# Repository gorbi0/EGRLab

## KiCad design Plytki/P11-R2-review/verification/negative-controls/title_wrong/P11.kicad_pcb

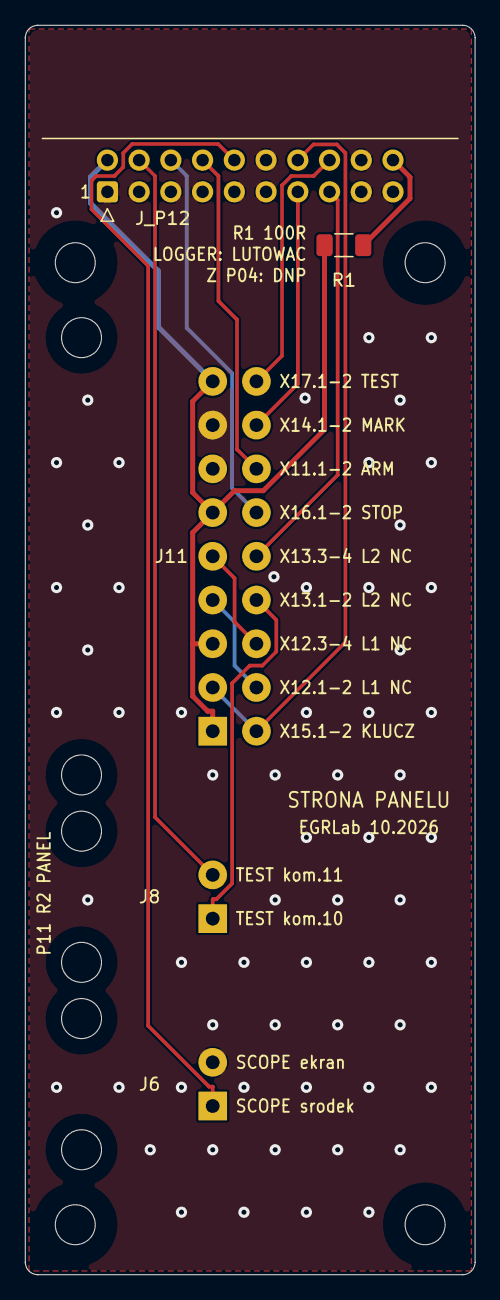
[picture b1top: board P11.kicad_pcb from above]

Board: 2 copper layers, 36.0 x 100.0 mm, 9 parts (0 on the bottom side), 14 nets.

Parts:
H1, H2, H3, H4: M3 NPTH
J6: SCOPE tail; FIELD_PAIR2
J8: TEST signal; FIELD_PAIR2
J11: CONTACTS; FIELD_CONTACT18
J_P12: IDC 2x10 katowe do P12; IDC-Header_2x10_P2.54mm_Horizontal
R1: 100R; R_1206_3216Metric_Pad1.30x1.75mm_HandSolder

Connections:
/3V3_IO: J_P12.20, R1.1
/CONTACTS/DIAG_L1_L2: J11.6, J11.9
/CONTACTS/ILK_L1_L2: J11.4, J11.7
/CONTACTS/LOOP_OUT: J8.1, J11.8
/N_J_SCOPE_HOT: J6.1, J_P12.10
ARM_CONTACT: J11.14, J_P12.8
GND: J6.2, J11.13, J11.15, J_P12.1, J_P12.3, J_P12.5, J_P12.7, J_P12.9, J_P12.11, J_P12.12, J_P12.17, J_P12.18, J_P12.19
LOGGER_CLEAR: J11.10, J_P12.15
MARK: J11.16, J_P12.13
MECH_OK: J8.2, J_P12.4
PANEL_3V3: J11.1, J11.5, J11.11, J11.17, J_P12.2, R1.2
STOP_NC_OUT: J11.12, J_P12.6
TEST_KEY: J11.2, J11.3, J_P12.14
TEST_PRESENT: J11.18, J_P12.16

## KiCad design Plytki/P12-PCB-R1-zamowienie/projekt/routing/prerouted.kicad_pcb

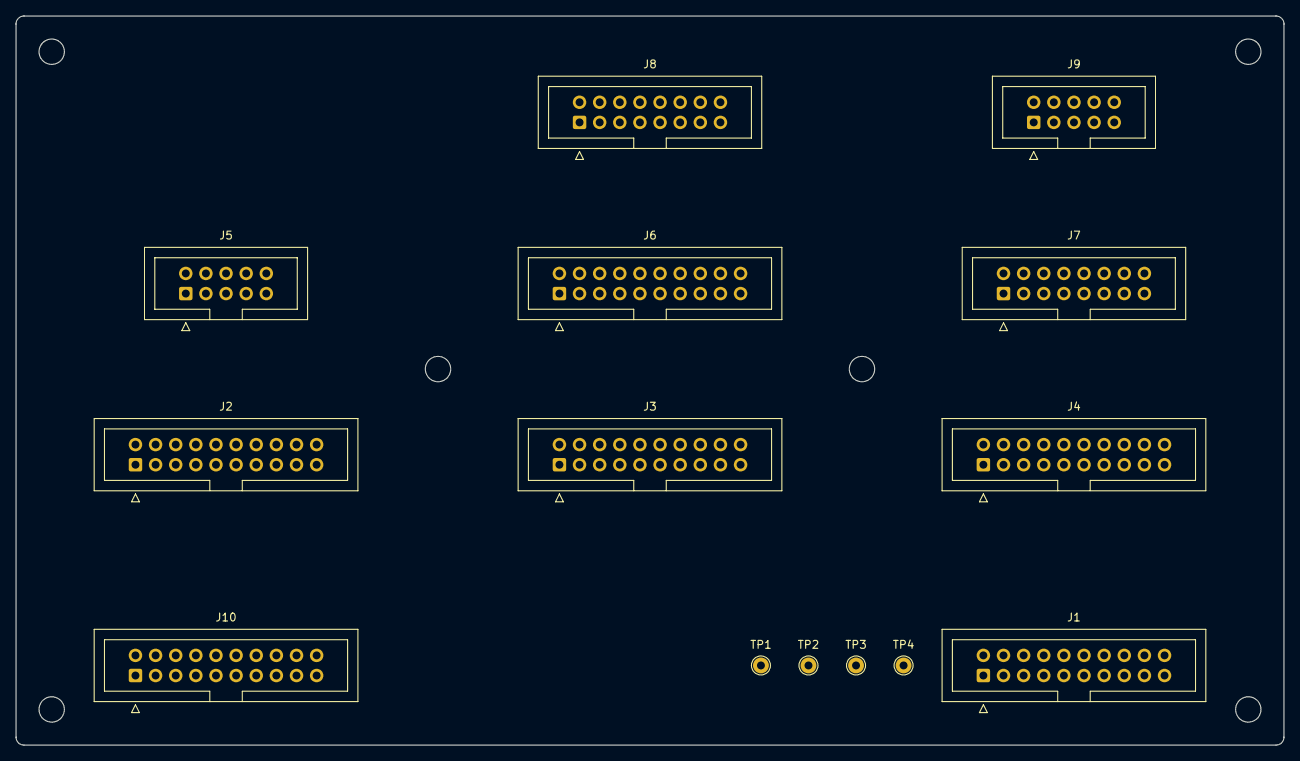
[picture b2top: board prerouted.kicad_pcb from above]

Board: 2 copper layers, 160.0 x 92.0 mm, 20 parts (0 on the bottom side), 27 nets, no tracks yet.

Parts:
H1, H2, H3, H4, H5, H6: M3 NPTH
J1: P02 J_BP; IDC-Header_2x10_P2.54mm_Vertical
J2: P03 J_BP1; IDC-Header_2x10_P2.54mm_Vertical
J3: P03 J_BP2; IDC-Header_2x10_P2.54mm_Vertical
J4: P03 J_BP3; IDC-Header_2x10_P2.54mm_Vertical
J5: P05 J_BP1; IDC-Header_2x05_P2.54mm_Vertical
J6: P05 J_BP2; IDC-Header_2x10_P2.54mm_Vertical
J7: P09 J1; IDC-Header_2x08_P2.54mm_Vertical
J8: P06 J_BP; IDC-Header_2x08_P2.54mm_Vertical
J9: P10 J1; IDC-Header_2x05_P2.54mm_Vertical
J10: P11 J_P12; IDC-Header_2x10_P2.54mm_Vertical
TP1, TP4: GND; TestPoint_THTPad_D2.0mm_Drill1.0mm
TP2: 5V_SYS; TestPoint_THTPad_D2.0mm_Drill1.0mm
TP3: 3V3_IO; TestPoint_THTPad_D2.0mm_Drill1.0mm

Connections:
3V3_IO: J1.8, J1.10, J4.5, J7.4, J8.14, J9.4, J10.20, TP3.1
5V_SYS: J1.2, J1.4, J1.6, J3.17, J3.19, J3.20, J5.2, J5.4, J7.2, J7.16, J8.10, J8.12, J9.2, J9.10, TP2.1
ADC_BUSY: J3.12, J6.12
ADC_CONVST: J3.10, J6.10
ADC_CS: J3.8, J6.8
ADC_DOUTA: J3.4, J6.4, J8.4
ADC_RESET: J3.18, J6.18
ADC_SCLK: J3.2, J6.2, J8.2
ADC_SDI: J3.6, J6.6
CAN_RX: J2.8, J9.8
CAN_TX: J2.6, J9.6
CS_ILOG_N: J2.2, J8.6
GND: J1.1, J1.3, J1.5, J1.7, J1.9, J1.11, J1.13, J1.19, J2.1, J2.3, J2.5, J2.7, J2.9, J3.1, J3.3, J3.5, J3.7, J3.9, J3.11, J3.13, J3.15, J4.1, J4.3, J4.7, J4.11, J4.15, J4.19, J5.1, J5.3, J5.5, J5.7, J5.8, J5.9, J6.1, J6.3, J6.5, J6.7, J6.9, J6.11, J6.13, J6.15, J6.16, J6.17, J6.19, J6.20, J7.1, J7.3, J7.5, J7.7, J7.9, J7.11, J7.13, J7.15, J8.1, J8.3, J8.5, J8.7, J8.9, J8.11, J8.13, J8.15, J8.16, J9.1, J9.3, J9.5, J9.7, J9.9, J10.1, J10.3, J10.5, J10.7, J10.9, J10.11, J10.12, J10.17, J10.18, J10.19, TP1.1, TP4.1
LOGGER_CLEAR: J2.15, J10.15
LOGGER_CURRENT_OK: J2.11, J8.8
MARK: J2.13, J10.13
MEAS_EN: J3.14, J6.14
N_J_SCOPE_HOT: J2.10, J10.10
PFAIL_N: J1.14, J3.16
SPI3_MISO: J4.6, J7.10
SPI3_MOSI: J4.4, J7.8
SPI3_SCLK: J4.2, J7.6
TC1_CS: J4.8, J7.12
TC2_CS: J4.10, J7.14
TEST_KEY: J2.14, J10.14
TEST_PRESENT: J2.16, J10.16
VBAT_SENSE: J1.20, J5.10

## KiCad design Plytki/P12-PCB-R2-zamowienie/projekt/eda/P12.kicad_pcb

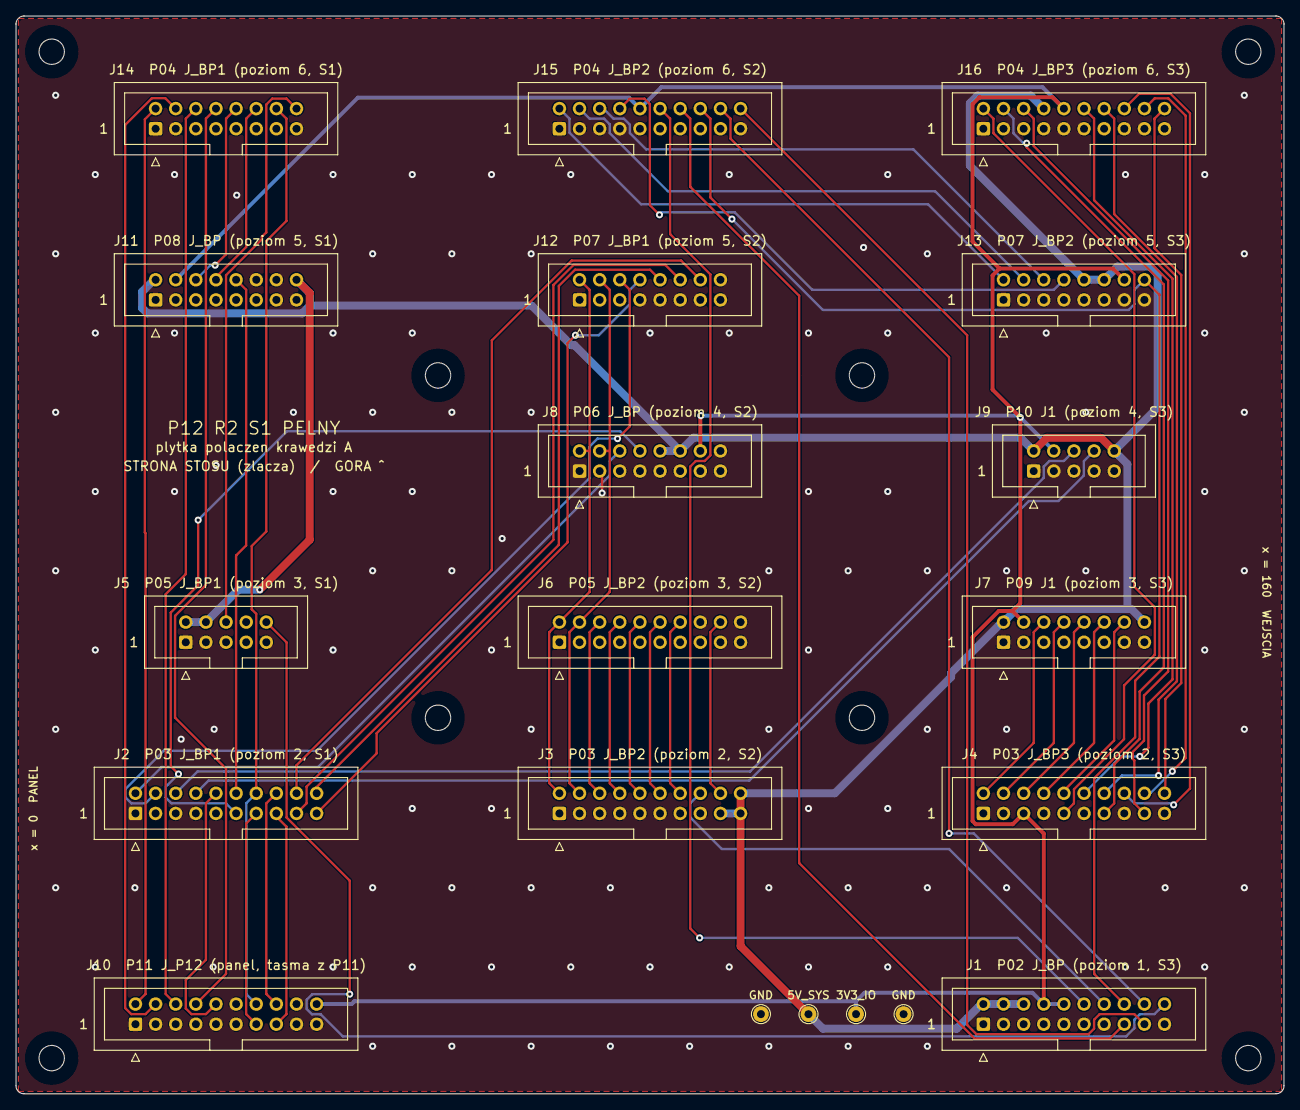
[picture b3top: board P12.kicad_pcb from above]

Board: 2 copper layers, 160.0 x 136.0 mm, 28 parts (0 on the bottom side), 57 nets.

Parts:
H1, H2, H3, H4, H5, H6, H7, H8: M3 NPTH
J1: P02 J_BP; IDC-Header_2x10_P2.54mm_Vertical
J2: P03 J_BP1; IDC-Header_2x10_P2.54mm_Vertical
J3: P03 J_BP2; IDC-Header_2x10_P2.54mm_Vertical
J4: P03 J_BP3; IDC-Header_2x10_P2.54mm_Vertical
J5: P05 J_BP1; IDC-Header_2x05_P2.54mm_Vertical
J6: P05 J_BP2; IDC-Header_2x10_P2.54mm_Vertical
J7: P09 J1; IDC-Header_2x08_P2.54mm_Vertical
J8: P06 J_BP; IDC-Header_2x08_P2.54mm_Vertical
J9: P10 J1; IDC-Header_2x05_P2.54mm_Vertical
J10: P11 J_P12; IDC-Header_2x10_P2.54mm_Vertical
J11: P08 J_BP; IDC-Header_2x08_P2.54mm_Vertical
J12: P07 J_BP1; IDC-Header_2x08_P2.54mm_Vertical
J13: P07 J_BP2; IDC-Header_2x08_P2.54mm_Vertical
J14: P04 J_BP1; IDC-Header_2x08_P2.54mm_Vertical
J15: P04 J_BP2; IDC-Header_2x10_P2.54mm_Vertical
J16: P04 J_BP3; IDC-Header_2x10_P2.54mm_Vertical
TP1, TP4: GND; TestPoint_THTPad_D2.0mm_Drill1.0mm
TP2: 5V_SYS; TestPoint_THTPad_D2.0mm_Drill1.0mm
TP3: 3V3_IO; TestPoint_THTPad_D2.0mm_Drill1.0mm

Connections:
3V3_IO: J1.8, J1.10, J4.5, J7.4, J8.14, J9.4, J10.20, J11.4, J13.14, J15.10, J16.10, TP3.1
5V_SYS: J1.2, J1.4, J1.6, J3.17, J3.19, J3.20, J5.2, J5.4, J7.2, J7.16, J8.10, J8.12, J9.2, J9.10, J11.2, J11.16, J13.10, J13.12, J16.8, TP2.1
ADC_BUSY: J3.12, J6.12
ADC_CONVST: J3.10, J6.10
ADC_CS: J3.8, J6.8
ADC_DOUTA: J3.4, J6.4, J8.4, J12.4
ADC_RESET: J3.18, J6.18
ADC_SCLK: J3.2, J6.2, J8.2, J12.2
ADC_SDI: J3.6, J6.6
ARM_CLK: J13.6, J15.6
ARM_CONTACT: J10.8, J14.8
CAN_RX: J2.8, J9.8
CAN_TX: J2.6, J9.6
CORE_LINK: J4.13, J16.4
CS_ILOG_N: J2.2, J8.6
CS_ITEST_N: J2.4, J12.6
DAQ_OK: J5.6, J14.16
DRIVE_OK: J13.8, J15.8
ENA_DIAG: J2.17, J12.12
ENB_DIAG: J2.18, J12.14
GND: J1.1, J1.3, J1.5, J1.7, J1.9, J1.11, J1.13, J1.19, J2.1, J2.3, J2.5, J2.7, J2.9, J3.1, J3.3, J3.5, J3.7, J3.9, J3.11, J3.13, J3.15, J4.1, J4.3, J4.7, J4.11, J4.15, J4.19, J5.1, J5.3, J5.5, J5.7, J5.8, J5.9, J6.1, J6.3, J6.5, J6.7, J6.9, J6.11, J6.13, J6.15, J6.16, J6.17, J6.19, J6.20, J7.1, J7.3, J7.5, J7.7, J7.9, J7.11, J7.13, J7.15, J8.1, J8.3, J8.5, J8.7, J8.9, J8.11, J8.13, J8.15, J8.16, J9.1, J9.3, J9.5, J9.7, J9.9, J10.1, J10.3, J10.5, J10.7, J10.9, J10.11, J10.12, J10.17, J10.18, J10.19, J11.1, J11.3, J11.5, J11.7, J11.9, J11.11, J11.12, J11.13, J11.14, J11.15, J12.1, J12.3, J12.5, J12.7, J12.9, J12.11, J12.13, J12.15, J12.16, J13.1, J13.3, J13.5, J13.7, J13.9, J13.11, J13.13, J13.15, J14.1, J14.3, J14.5, J14.7, J14.9, J14.11, J14.13, J14.15, J15.1, J15.3, J15.5, J15.7, J15.9, J15.11, J15.13, J15.15, J15.17, J15.19, J16.1, J16.3, J16.5, J16.7, J16.9, J16.11, J16.13, J16.15, J16.17, J16.19, TP1.1, TP4.1
HEARTBEAT: J4.16, J16.16
HW_ARMED: J4.17, J16.6
INTERLOCK: J4.20, J16.20
LOGGER_CLEAR: J2.15, J10.15
LOGGER_CURRENT_OK: J2.11, J8.8
MARK: J2.13, J10.13
MCU_ARM: J4.18, J16.18
MEAS_EN: J3.14, J6.14
MECH_OK: J10.4, J14.4
MOTOR_INA: J2.19, J12.8
MOTOR_INB: J2.20, J12.10
MOTOR_PERMIT: J13.2, J15.2
N_J_SCOPE_HOT: J2.10, J10.10
P04_3V3: J1.15, J15.14
PANEL_3V3: J10.2, J14.2
PFAIL_N: J1.14, J3.16
PG_LINK: J1.18, J15.18
PG_SEND: J1.17, J15.20
PSU_OK: J1.12, J15.12
PWM: J4.14, J16.14
PWM_OUT: J13.4, J15.4
SAFE_N: J1.16, J13.16, J15.16
SENSOR_ENABLE: J4.9, J16.2
SENSOR_HEALTHY: J2.12, J11.10
SENSOR_OK: J11.8, J14.12
SENSOR_PERMIT: J11.6, J14.10
SPI3_MISO: J4.6, J7.10
SPI3_MOSI: J4.4, J7.8
SPI3_SCLK: J4.2, J7.6
STOP_NC_OUT: J10.6, J14.6
SUP_N_OUT: J4.12, J16.12
TC1_CS: J4.8, J7.12
TC2_CS: J4.10, J7.14
TEST_KEY: J2.14, J10.14, J14.14
TEST_PRESENT: J2.16, J10.16
VBAT_SENSE: J1.20, J5.10
